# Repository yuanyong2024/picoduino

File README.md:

# Introduction
This is a Raspberry Pi Pico W hardware in arduino form factor.And it's name is picoduino

Unlike all the other wireless solutions for RP2040 on market(which almost all use the ESP wireless chip).
This board is equipped with a module that have the same chipsets like Pico W from Raspberry Pi. A microcontroller RP2040 from Raspberry Pi and a wireless chip CY43439 from Infineon.

# Features
1. totally compatible with arduino form factor.
2. fw developed for pico  w can easily ported to picoduino without any change(especially all the wireless features).
3. using analog switch so that 3 ADC ports can connect to 6 pins from A0 to A5 on picoduino board.
4. use a dedicated voltage reference to improve the accuracy of the ADC.
5. use two DC-DC regulators instead of LDO to improve the efficiency as well as increasing the maximum input voltage to 24V.
6. exposed all the GPIOs from RP2040 chip.
7. USB type C interface.
8. all the deisgn files are open-sourced and designed in Kicad.
    
# Limitations
1. During my test, I found out the antenna's performance still cannot match the official Pico w.
2. Still need more time and energy to tuning the antenna
3. No shield cover for the module on this version yet.
   
# considering support me?
Building the module and the picoduino definitley take time and energy.And also it's cost a lot. The module itself is a six layer board and I'm using the expensive Infineon chip. 
So I would appreciate anyone who can support me by purchase it from [this link](https://www.elecrow.com/picoduino.html)

# setup
For every board that you purchased, it's preflashed with a fw that can easily connect to local network as long as the wifi is available.
1. Plug picoduino to computer via USB type C cable.(A serial port should be available now)
2. Use some serial debug tool like arduino IDE's tool and type in your local WiFi name and then click send to send the WiFi name to picoduino.
3. it then will show the input WiFi name and ask you to type the password.
4. And send the password, picoduino will try to connect to the WiFi network with quick blink green led.
5. Once success, it will keep the green led on and you can copy the ip address to browser and then hit enter.
6. A webpage for controlling the green led is alive and you can control the led by click the webpage buttons.

# What's next?
After this picoduino, I will design a adafruit feather compatible one by using the same pico w module.
I will also make a programmable power supplier shield for picoduino.
## Stay tuned!

# useful links:
[pico w datasheet](https://datasheets.raspberrypi.com/picow/pico-w-datasheet.pdf?_gl=1*pez2dw*_ga*NTM5ODUxMTkxLjE3MTE2MzI0NTI.*_ga_22FD70LWDS*MTcxMTYzMjQ1Mi4xLjAuMTcxMTYzMjQ1Mi4wLjAuMA..)

[raspberry pi pico documentation](https://www.raspberrypi.com/documentation/microcontrollers/raspberry-pi-pico.html#raspberry-pi-pico-w)

[pico w module design file](https://github.com/yuanyong2024/pico_w_module)

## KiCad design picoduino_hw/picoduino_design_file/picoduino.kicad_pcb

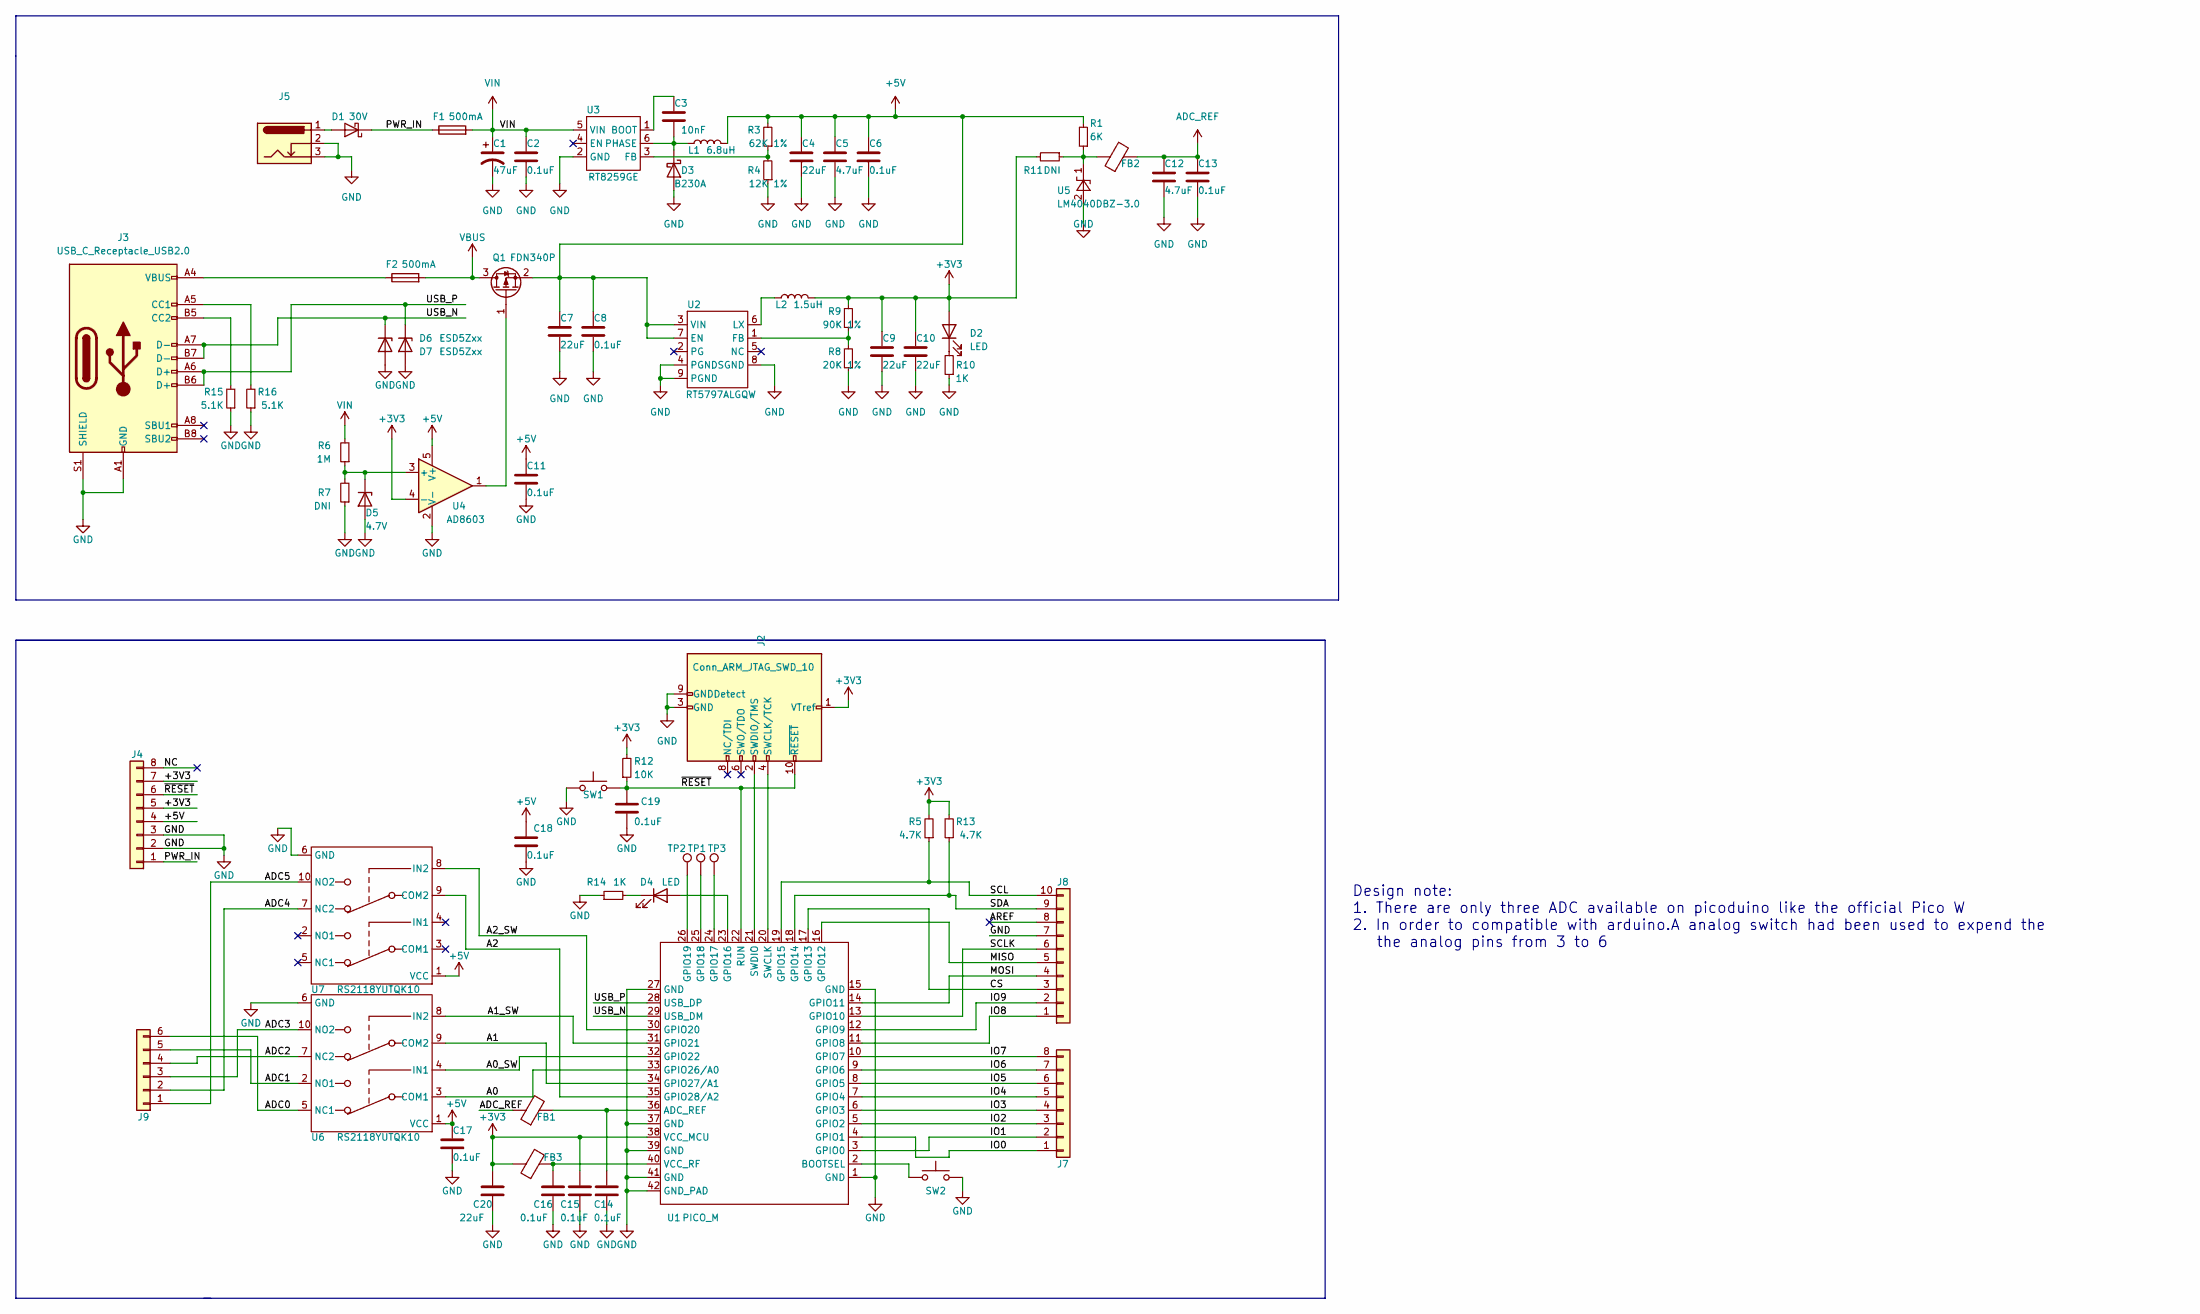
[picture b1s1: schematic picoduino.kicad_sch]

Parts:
C1: 47uF; CP_Elec_4x3
C2, C6, C8, C11, C13, C14, C15, C16, C17, C18, C19: 0.1uF; C_0603_1608Metric
C3: 10nF; C_0603_1608Metric
C4, C7, C9, C10, C20: 22uF; C_0603_1608Metric
C5, C12: 4.7uF; C_0603_1608Metric
D1: 30V; D_SMA
D2, D4: LED; LED_0603_1608Metric
D3: B230A; D_SOD-123F
D5: 4.7V; D_SOD-123F
D6, D7: ESD5Zxx; D_SOD-523
F1: 500mA; Fuse_1206_3216Metric
F2: 500mA; Fuse_0805_2012Metric
FB1, FB2, FB3: FerriteBead; L_0603_1608Metric
J2: Conn_ARM_JTAG_SWD_10; PinHeader_2x05_P1.27mm_Vertical_SMD
J3: USB_C_Receptacle_USB2.0; USB_C_Receptacle_HRO_TYPE-C-31-M-12
J4, J7: Conn_01x08; PinSocket_1x08_P2.54mm_Vertical
J5: Barrel_Jack_Switch_Pin3Ring; BarrelJack_GCT_DCJ200-10-A_Horizontal
J8: Conn_01x10; PinSocket_1x10_P2.54mm_Vertical
J9: Conn_01x06; PinSocket_1x06_P2.54mm_Vertical
L1: 6.8uH; L_Abracon_ASPI-4030S
L2: 1.5uH; L_Abracon_ASPI-3012S
Q1: FDN340P; SOT-23
R1: 6K; R_0805_2012Metric
R3: 62K 1%; R_0603_1608Metric
R4: 12K 1%; R_0603_1608Metric
R5, R13: 4.7K; R_0603_1608Metric
R6: 1M; R_0603_1608Metric
R7, R11: DNI; R_0603_1608Metric
R8: 20K 1%; R_0603_1608Metric
R9: 90K 1%; R_0603_1608Metric
R10, R14: 1K; R_0603_1608Metric
R12: 10K; R_0603_1608Metric
R15, R16: 5.1K; R_0603_1608Metric
SW1, SW2: SW_Push_SPST_NO_Alps_SKRK
TP1, TP2, TP3: TestPoint; TestPoint_Pad_D1.5mm
U1: PICO_M
U2: RT5797ALGQW; DFN-8-1EP_2x2mm_P0.5mm_EP0.6x1.2mm
U3: RT8259GE; SOT-23-6
U4: AD8603; TSOT-23-5
U5: LM4040DBZ-3.0; SOT-23-3
U6, U7: RS2118YUTQK10; UQFN-10_1.4x1.8mm_P0.4mm

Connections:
+1V2: C1.1, C2.1, F1.2, R6.2, U3.5 (VIN)
+3V3: C9.2, C10.2, C15.2, C20.2, D2.2 (A), FB3.1, J2.1 (VTref), J4.5, J4.7, L2.2, R5.2, R9.2, R11.2, R12.2, R13.2, U1.38 (VCC_MCU), U4.4 (-)
+5V: C4.2, C5.2, C6.2, C7.2, C8.2, C11.2, C17.2, C18.2, J4.4, L1.2, Q1.2 (S), R1.2, R3.2, U2.3 (VIN), U2.7 (EN), U4.5 (V+), U6.1 (VCC), U7.1 (VCC)
/A0: U1.33 (GPIO26/A0), U6.3 (COM1)
/A0_SW: U1.32 (GPIO22), U6.4 (IN1)
/A1: U1.34 (GPIO27/A1), U6.9 (COM2)
/A1_SW: U1.31 (GPIO21), U6.8 (IN2)
/A2: U1.35 (GPIO28/A2), U7.9 (COM2)
/A2_SW: U1.30 (GPIO20), U7.8 (IN2)
/ADC0: J9.6, U6.5 (NC1)
/ADC1: J9.5, U6.2 (NO1)
/ADC2: J9.4, U6.7 (NC2)
/ADC3: J9.3, U6.10 (NO2)
/ADC4: J9.2, U7.7 (NC2)
/ADC5: J9.1, U7.10 (NO2)
/AREF: J8.8
/CS: J8.3, U1.17 (GPIO13)
/IO0: J7.1, U1.4 (GPIO1)
/IO1: J7.2, U1.3 (GPIO0)
/IO2: J7.3, U1.5 (GPIO2)
/IO3: J7.4, U1.6 (GPIO3)
/IO4: J7.5, U1.7 (GPIO4)
/IO5: J7.6, U1.8 (GPIO5)
/IO6: J7.7, U1.9 (GPIO6)
/IO7: J7.8, U1.10 (GPIO7)
/IO8: J8.1, U1.11 (GPIO8)
/IO9: J8.2, U1.12 (GPIO9)
/MISO: J8.5, U1.16 (GPIO12)
/MOSI: J8.4, U1.14 (GPIO11)
/NC: J4.8
/PWR_IN: D1.1 (K), F1.1, J4.1
/SCL: J8.10, R5.1, U1.19 (GPIO15)
/SCLK: J8.6, U1.13 (GPIO10)
/SDA: J8.9, R13.1, U1.18 (GPIO14)
/USB_N: D6.1 (K), J3.A7 (D-), J3.B7 (D-), U1.29 (USB_DM)
/USB_P: D7.1 (K), J3.A6 (D+), J3.B6 (D+), U1.28 (USB_DP)
/~RESET: C19.2, J2.10 (~RESET), J4.6, R12.1, SW1.1, U1.22 (RUN)
ADC_REF: C12.2, C13.2, FB1.1, FB2.2; also elsewhere on the board
GND: C1.2, C2.2, C4.1, C5.1, C6.1, C7.1, C8.1, C9.1, C10.1, C11.1, C12.1, C13.1, C14.1, C15.1, C16.1, C17.1, C18.1, C19.1, C20.1, D3.2 (A), D5.2 (A), D6.2 (A), D7.2 (A), J2.3 (GND), J2.5 (GND), J2.9 (GNDDetect), J3.A1 (GND), J3.A12 (GND), J3.B1 (GND), J3.B12 (GND), J3.S1 (SHIELD), J4.2, J4.3, J5.2, J5.3, J8.7, R4.1, R7.1, R8.1, R10.1, R14.1, R15.1, R16.1, SW1.2, SW2.2, U1.1 (GND), U1.15 (GND), U1.27 (GND), U1.37 (GND), U1.39 (GND), U1.41 (GND), U1.42 (GND_PAD), U2.4 (PGND), U2.8 (SGND), U2.9 (PGND), U3.2 (GND), U4.2 (V-), U5.2 (A), U6.6 (GND), U7.6 (GND)
unnamed: D1.2 (A), J5.1
unnamed: D2.1 (K), R10.2
unnamed: C3.1, D3.1 (K), L1.1, U3.6 (PHASE)
unnamed: D4.2 (A), U1.23 (GPIO16)
unnamed: D4.1 (K), R14.2
unnamed: D5.1 (K), R6.1, R7.2, U4.3 (+)
unnamed: F2.1, J3.A4 (VBUS), J3.A9 (VBUS), J3.B4 (VBUS), J3.B9 (VBUS)
unnamed: J2.4 (SWCLK/TCK), U1.20 (SWCLK)
unnamed: J2.2 (SWDIO/TMS), U1.21 (SWDIO)
unnamed: J3.A5 (CC1), R16.2
unnamed: J3.B5 (CC2), R15.2
unnamed: Q1.1 (G), U4.1
unnamed: C14.2, FB1.2, U1.36 (ADC_REF)
unnamed: SW2.1, U1.2 (BOOTSEL)
unnamed: TP1.1, U1.24 (GPIO17)
unnamed: TP3.1, U1.25 (GPIO18)
unnamed: TP2.1, U1.26 (GPIO19)
unnamed: C16.2, FB3.2, U1.40 (VCC_RF)
unnamed: R8.2, R9.1, U2.1 (FB)
unnamed: L2.1, U2.6 (LX)
unnamed: C3.2, U3.1 (BOOT)
unnamed: R3.1, R4.2, U3.3 (FB)
unnamed 61: FB2.1, R1.1, R11.1, U5.1 (K); also elsewhere on the board
VBUS: F2.2, Q1.3 (D)

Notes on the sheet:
Design note: 1. There are only three ADC available on picoduino like the official Pico W 2. In order to compatible with arduino.A analog switch had been used to expend the the analog pins from 3 to 6

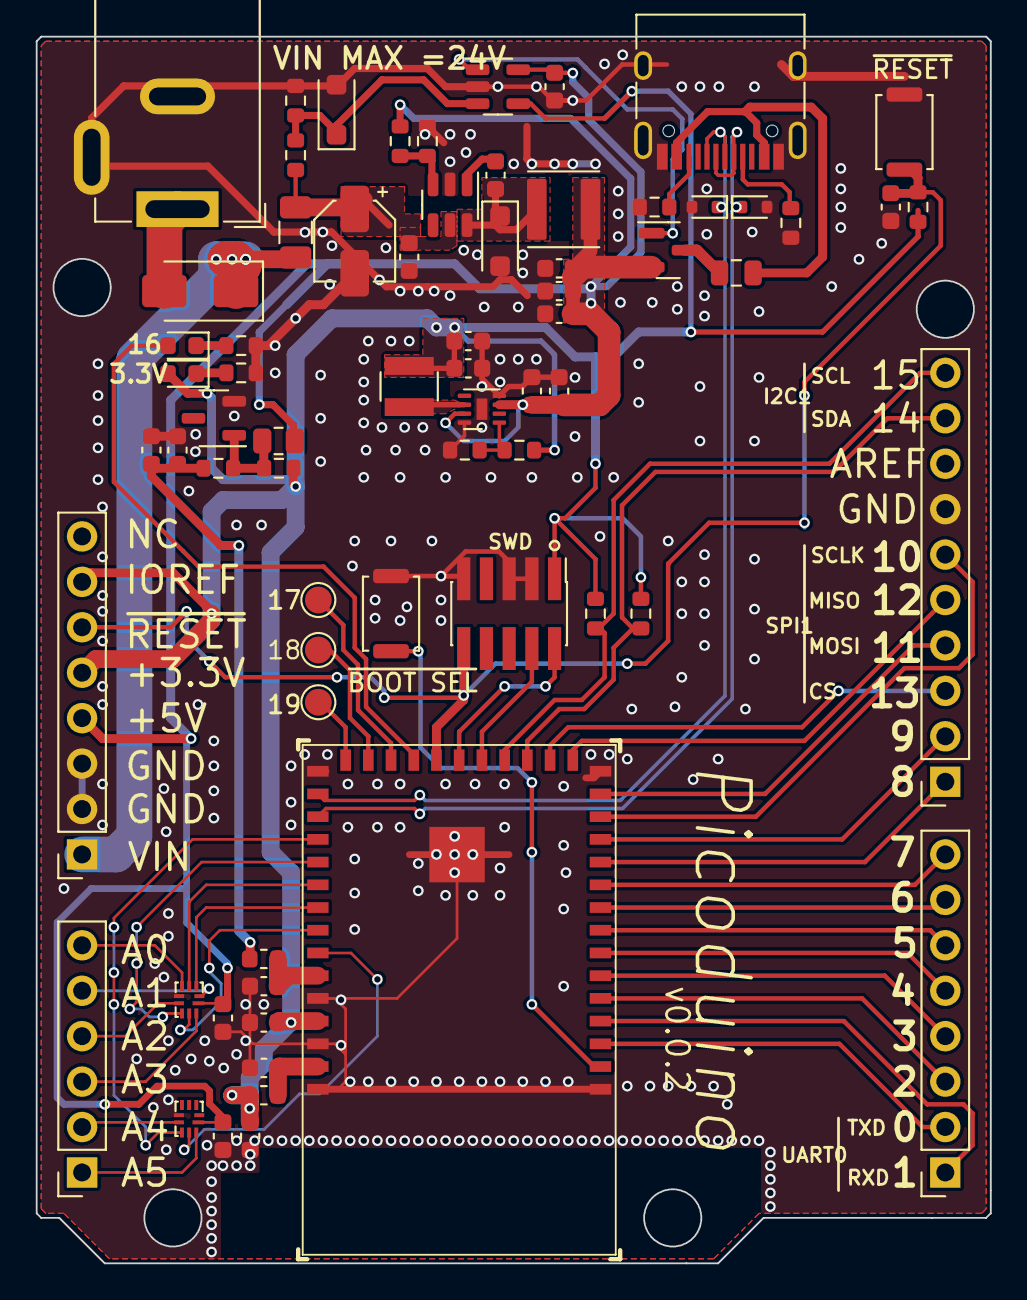
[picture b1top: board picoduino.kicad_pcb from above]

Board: 2 copper layers, 53.3 x 68.6 mm, 69 parts (0 on the bottom side), 61 nets.

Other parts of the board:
R2: 0R; R_0603_1608Metric

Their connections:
ADC_REF: R2.1; also elsewhere on the board
unnamed 61: R2.2; also elsewhere on the board

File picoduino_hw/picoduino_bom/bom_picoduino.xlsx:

Ref | Qnty | Value | Footprint | PN | Vendor | Price(MOQ=100)
C1 | 1 | 47uF | Capacitor_SMD:CP_Elec_4x3 | EEEFT1V220AR | SAMSUNG | 1.02
C2, C6, C8, C11, C13, C14, C15, C16, C17, C18, C19 | 11 | 0.1uF | Capacitor_SMD:C_0603_1608Metric | 0603B104K500NT | FH | 0.014
C3 | 1 | 10nF | Capacitor_SMD:C_0603_1608Metric | 0603B103K500NT | FH | 0.015
C4,C7, C9, C20,C10 | 5 | 22uF | Capacitor_SMD:C_0603_1608Metric | CL10A226MP8NUNE | SAMSUNG | 0.084
C5, C12 | 2 | 4.7uF | Capacitor_SMD:C_0603_1608Metric | CL10A475KO8NNNC | SAMSUNG | 0.065
D1 | 1 | 30V | Diode_SMD:D_SMB | SSB44-E3/52T | VISHAY | 0.7
D2 | 1 | RED LED | LED_SMD:LED_0603_1608Metric | 19-213/R6C-AP1Q2B/5T | EVERLIGHT | 0.17
D4 | 1 | GREEN LED | LED_SMD:LED_0603_1608Metric | 19-213/GHC-XS1T1N/5T | EVERLIGHT | 0.3
D3 | 1 | 3A | Diode_SMD:D_SOD-123F | DSK34 | TWGMC | 0.16
D5 | 1 | 4.7V | Diode_SMD:D_SOD-123F | MMSZ4688T1G | onsemi | 0.27
D6, D7 | 2 | ESD5Zxx | Diode_SMD:D_SOD-523 | PESD5V0S1BB | TECH PUBLIC | 0.11
F1 | 1 | 500mA | Fuse:Fuse_1206_3216Metric | nSMD050-33V | luhai | 0.25
F2 | 1 | 500mA | Fuse:Fuse_0805_2012Metric | SMD0805B050TF | Brightking | 0.11
FB1, FB2, FB3 | 3 | FerriteBead | Inductor_SMD:L_0603_1608Metric | BLM18AG601SN1D | muRata | 0.037
J2 | 1 | Conn_ARM_JTAG_SWD_10 | Connector_PinHeader_1.27mm:PinHeader_2x05_P1.27mm_Vertical_SMD | HB-PH9-12725PB2GOB | HANBO | 0.45
J3 | 1 | USB_C_Receptacle_USB2.0 | Connector_USB:USB_C_Receptacle_HRO_TYPE-C-31-M-12 | TYPE-C 16PIN 2MD(073) | SHOU HAN | 0.28
J4, J7 | 2 | Conn_01x08 | Connector_PinSocket_2.54mm:PinSocket_1x08_P2.54mm_Vertical | PM254-1-08-Z-8.5 | HCTL | 0.65
J5 | 1 | Barrel_Jack_Switch_Pin3Ring | Connector_BarrelJack:BarrelJack_GCT_DCJ200-10-A_Horizontal | DC-005-20A | HRO | 0.46
J8 | 1 | Conn_01x10 | Connector_PinSocket_2.54mm:PinSocket_1x10_P2.54mm_Vertical | PM254-1-10-Z-8.5 | HCTL | 0.77
J9 | 1 | Conn_01x06 | Connector_PinSocket_2.54mm:PinSocket_1x06_P2.54mm_Vertical | PM254-1-06-W-8.5 | HCTL | 0.61
L1 | 1 | 6.8uH | Inductor_SMD:L_Abracon_ASPI-4030S | YHNR4020-6R8M | YJYCOIN | 0.45
L2 | 1 | 1.5uH | Inductor_SMD:L_Abracon_ASPI-3012S | FNR3012S1R5NT | CJIANG | 0.212
Q1 | 1 | FDN340P | Package_TO_SOT_SMD:SOT-23 | FDN340P | TECH PUBLIC | 0.3
R1 | 1 | 6K | Resistor_SMD:R_0805_2012Metric | 0603WAF1002T5E | UNI-ROYAL | 0.0057
R3 | 1 | 62K 1% | Resistor_SMD:R_0603_1608Metric | 0603WAF6202T5E | UNI-ROYAL | 0.0067
R4 | 1 | 12K 1% | Resistor_SMD:R_0603_1608Metric | 0603WAF1202T5E | UNI-ROYAL | 0.0061
R5, R13 | 2 | 4.7K | Resistor_SMD:R_0603_1608Metric | 0603WAF4701T5E | UNI-ROYAL | 0.0065
R12 | 1 | 10K | Resistor_SMD:R_0603_1608Metric | 0603WAF1002T5E | UNI-ROYAL | 0.0057
R6 | 1 | 1M | Resistor_SMD:R_0603_1608Metric | 0603WAF1004T5E | UNI-ROYAL | 0.006
R7, R11 | 2 | DNI | Resistor_SMD:R_0603_1608Metric
R8 | 1 | 20K 1% | Resistor_SMD:R_0603_1608Metric | 0603WAF2002T5E | UNI | 0.006
R9 | 1 | 90K 1% | Resistor_SMD:R_0603_1608Metric | 0603WAF9002T5E | UNI-ROYAL | 0.006
R10, R14 | 2 | 1K | Resistor_SMD:R_0603_1608Metric | 0603WAF1001T5E | UNI-ROYAL | 0.005
R15, R16 | 2 | 5.1K | Resistor_SMD:R_0603_1608Metric | 0603WAF5101T5E | UNI-ROYAL | 0.006
SW1, SW2 | 2 | ~ | Button_Switch_SMD:SW_Push_SPST_NO_Alps_SKRK | YTS1C0191ABG00N | YIYUAN | 0.46
U1 | 1 | PICO_M | kiCadPcbLib:PICO_M
U2 | 1 | RT5797ALGQW | Package_DFN_QFN:DFN-8-1EP_2x2mm_P0.5mm_EP0.6x1.2mm | RT5797ALGQW | RICHTEK | 1.6
U3 | 1 | RT8259GE | Package_TO_SOT_SMD:SOT-23-6 | RT8259GE | RICHTEK | 2.5
U4 | 1 | OP | Package_TO_SOT_SMD:TSOT-23-5 | TL081HIDBVR | TI | 0.7
U5 | 1 | LM4040DBZ-3.0 | Package_TO_SOT_SMD:SOT-23-3 | LM4040B30FTA | DIODES | 2.84
U6, U7 | 2 | RS2118YUTQK10 | Package_DFN_QFN:UQFN-10_1.4x1.8mm_P0.4mm | RS2118YUTQK10 | RUNIC | 1.55
